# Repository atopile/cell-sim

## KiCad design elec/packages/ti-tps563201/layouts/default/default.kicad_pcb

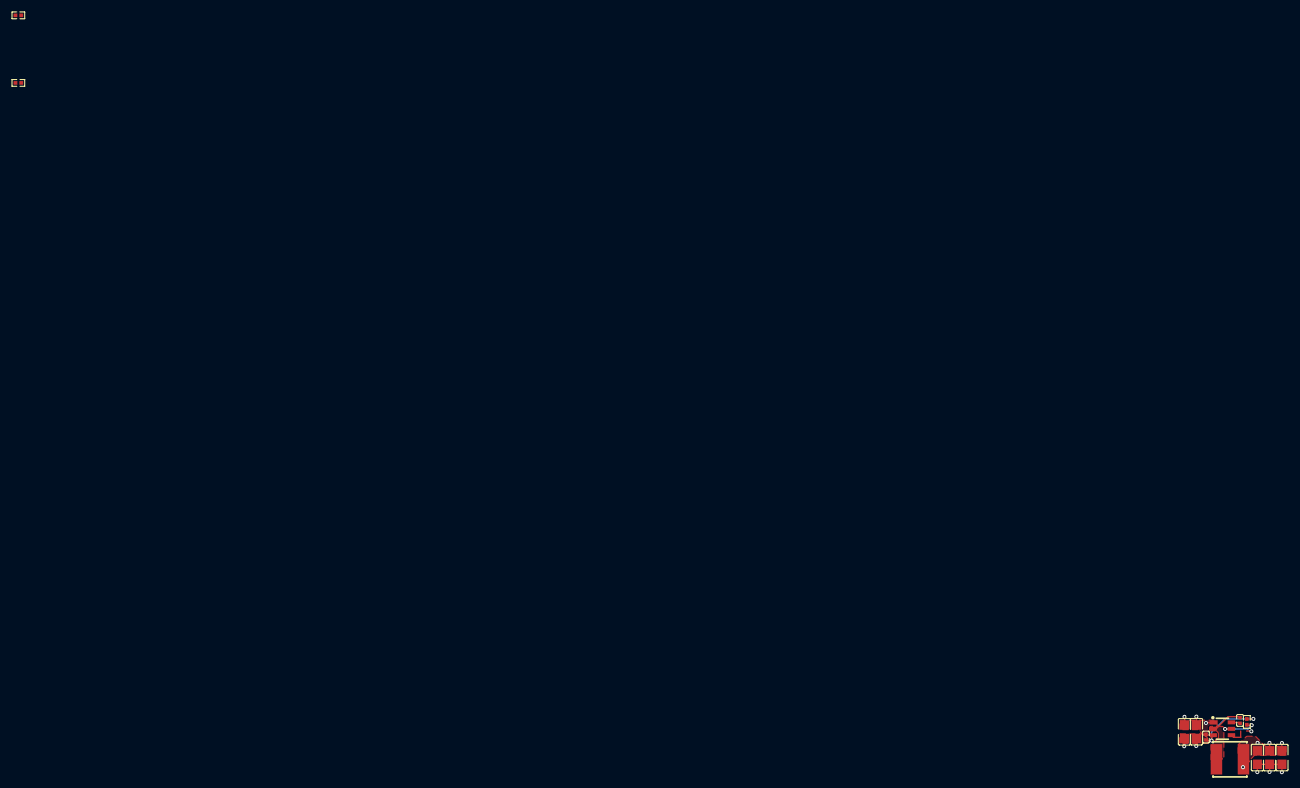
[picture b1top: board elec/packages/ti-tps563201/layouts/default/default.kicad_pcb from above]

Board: 2 copper layers, 12 parts (0 on the bottom side), 7 nets.

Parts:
C1, C4: 100nF; C0402
C2, C3, C5, C6, C7: 10µF; C0805
L1: L 2.2µH; IND-SMD_L5.0-W5.0_FNR5012S
R1, R2, R3: 10kΩ; R0402
U1: SOT-23-6_L2.9-W1.6-P0.95-LS2.8-BR

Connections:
EN: R1.1, U1.5
hv: C1.2, U1.6
input_caps[2]-power-hv: C2.1, C3.1, C4.2, R1.2, U1.3
lv: C1.1, L1.1, U1.2
output_caps[2]-power-hv: C5.1, C6.1, C7.1, L1.2, R2.1
output_caps[2]-power-lv: C2.2, C3.2, C4.1, C5.2, C6.2, C7.2, R3.2, U1.1
ref_out-hv: R2.2, R3.1, U1.4

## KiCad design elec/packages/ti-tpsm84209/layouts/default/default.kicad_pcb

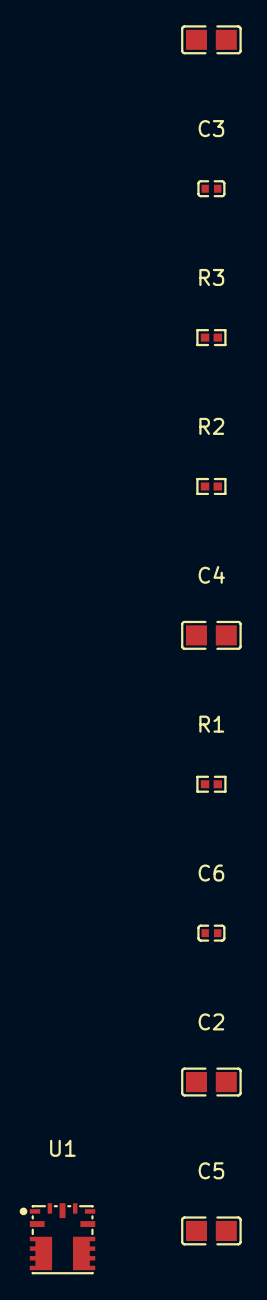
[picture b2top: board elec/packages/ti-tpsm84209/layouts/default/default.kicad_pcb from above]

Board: 2 copper layers, 10 parts (0 on the bottom side), 7 nets, no tracks yet.

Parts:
C1, C2: 10µF; C0805
C3, C6: 100nF; C0402
C4, C5: 22µF; C0805
R1: 10kΩ; R0402
R2: 100kΩ; R0402
R3: 52.3kΩ; R0402
U1: QFN-9_L4.5-W4.0_TPSM84209RKHR

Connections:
DNC: U1.6, U1.7
EN: R2.2, U1.9
FB: R1.1, R3.2, U1.1
SW: U1.4, U1.5
cout_hf-power-hv: C4.1, C5.1, C6.1, R3.1, U1.3
hv: C1.1, C2.1, C3.1, R2.1, U1.2
lv: C1.2, C2.2, C3.2, C4.2, C5.2, C6.2, R1.2, U1.8

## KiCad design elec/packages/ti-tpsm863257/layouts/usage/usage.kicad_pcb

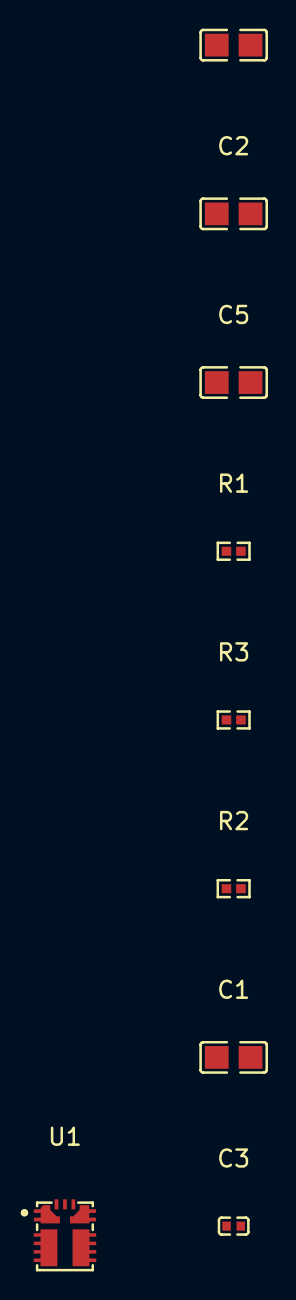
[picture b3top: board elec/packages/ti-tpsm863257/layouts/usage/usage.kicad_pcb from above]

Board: 2 copper layers, 9 parts (0 on the bottom side), 5 nets, no tracks yet.

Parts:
C1, C2: 10µF; C0805
C3: 100nF; C0402
C4, C5: 22µF; C0805
R1: 10kΩ; R0402
R2: 100kΩ; R0402
R3: 73.2kΩ; R0402
U1: QFN-7_L4.0-W3.3_TPSM863257RDXR

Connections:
FB: R1.1, R3.2, U1.7
PG: R2.2, U1.5
c_out[1]-power-hv: C4.1, C5.1, R2.1, R3.1, U1.3
hv: C1.1, C2.1, C3.1, U1.1
lv: C1.2, C2.2, C3.2, C4.2, C5.2, R1.2, U1.4

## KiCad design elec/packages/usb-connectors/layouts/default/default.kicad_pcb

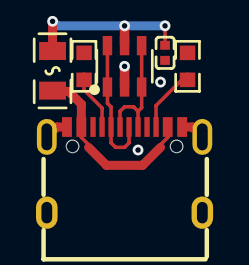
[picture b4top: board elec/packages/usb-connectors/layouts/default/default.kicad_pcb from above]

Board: 2 copper layers, 6 parts (0 on the bottom side), 7 nets.

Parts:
C2: 100nF; C0402
D1: SOT-23-6_L2.9-W1.6-P0.95-LS2.8-BL
F2: F0805
R1, R2: 10kΩ; R0603
X1: USB-C-SMD_TYPE-C-6PIN-2MD-073

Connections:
4: R1.1, X1.4
10: R2.1, X1.10
DATA_N: D1.1, D1.6, X1.5, X1.7
DATA_P: D1.3, D1.4, X1.6, X1.8
hv: F2.1, X1.2, X1.11
lv: C2.2, D1.2, R1.2, R2.2, X1.1, X1.12, X1.13, X1.14, X1.15, X1.16
power-hv: C2.1, D1.5, F2.2

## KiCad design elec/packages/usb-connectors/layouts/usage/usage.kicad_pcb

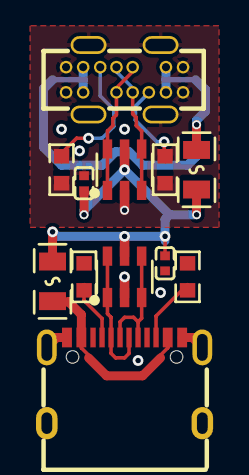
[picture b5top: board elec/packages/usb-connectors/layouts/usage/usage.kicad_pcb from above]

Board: 2 copper layers, 12 parts (0 on the bottom side), 12 nets.

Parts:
C2, C4: 100nF; C0402
D1, D2: SOT-23-6_L2.9-W1.6-P0.95-LS2.8-BL
F2, F4: F0805
R1, R2, R3, R4: 10kΩ; R0603
USB1: USB-C-SMD_TYPE-C-6PIN-2MD-073
USBC1: USB-C-TH_TYPE-C-USB-14P

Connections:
4: R1.1, USB1.4
5: R4.1, USBC1.5
10: R2.1, USB1.10
12: R3.1, USBC1.12
DATA_N: D1.1, D1.6, USB1.5, USB1.7
DATA_P: D1.3, D1.4, USB1.6, USB1.8
connector-power_vbus-hv: F2.1, USB1.2, USB1.11
connector-power_vbus-hv-1: F4.1, USBC1.2, USBC1.6, USBC1.9, USBC1.13
hv: C2.1, C4.1, D1.5, D2.5, F2.2, F4.2
lv: C2.2, C4.2, D1.2, D2.2, R1.2, R2.2, R3.2, R4.2, USB1.1, USB1.12, USB1.13, USB1.14, USB1.15, USB1.16, USBC1.0, USBC1.1, USBC1.7, USBC1.8, USBC1.14, USBC1.15, USBC1.16, USBC1.17
usb_connector_vertical-usb-DATA_N: D2.1, D2.6, USBC1.3, USBC1.10
usb_connector_vertical-usb-DATA_P: D2.3, D2.4, USBC1.4, USBC1.11

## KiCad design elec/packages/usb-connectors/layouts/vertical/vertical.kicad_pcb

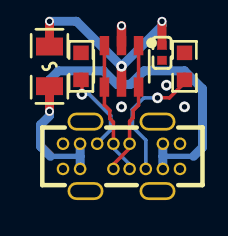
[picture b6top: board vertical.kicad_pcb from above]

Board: 2 copper layers, 6 parts (0 on the bottom side), 7 nets.

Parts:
C2: 100nF; C0402
D1: SOT-23-6_L2.9-W1.6-P0.95-LS2.8-BL
F1: F0805
R1, R2: 10kΩ; R0603
X1: USB-C-TH_TYPE-C-USB-14P

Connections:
5: R2.1, X1.5
12: R1.1, X1.12
DATA_N: D1.1, D1.6, X1.3, X1.10
DATA_P: D1.3, D1.4, X1.4, X1.11
hv: F1.1, X1.2, X1.6, X1.9, X1.13
lv: C2.2, D1.2, R1.2, R2.2, X1.0, X1.1, X1.7, X1.8, X1.14, X1.15, X1.16, X1.17
power-hv: C2.1, D1.5, F1.2
